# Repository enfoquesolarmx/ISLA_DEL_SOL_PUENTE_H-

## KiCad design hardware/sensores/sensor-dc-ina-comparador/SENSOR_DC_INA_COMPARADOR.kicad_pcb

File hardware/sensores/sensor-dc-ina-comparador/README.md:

# SENSOR_DC_INA_COMPARADOR — módulo de medición, límite y protección de corriente DC

- **Proyecto:** Puente H — prototipo SPWM "Isla del Sol" (inversor 48 V → 127 V / 60 Hz, 1000 W; modo cargador 1 kVA)
- **Módulo:** sensor de corriente del **bus DC**, **bidireccional** (descarga e inyección/carga), con **dos ventanas por hardware**: disparo duro y límite de corriente, más **detección de presencia fail-safe** (SENSOR_OK)
- **Versión:** **V0.2** (serigrafía: `V.0.2/8-NOV-26.J.G`) · **Fecha:** 2026-11-08
- **Estado:** esquemático y layout V0.2 terminados, ERC/DRC sin errores. Pendiente: fabricación y validación en banco
- **Compatible con:** ATmega328P, ATmega4809, STM32, ESP32 y otros MCU de 3.3 V o 5 V, sin cambiar piezas
- **Decisiones que implementa:** [DC-014](../../../docs/decisiones_criticas.md#dc-014-corte-del-pwm-por-hardware-con-lógica-fail-safe-sensor_ok-y-doble-candado) (SENSOR_OK fail-safe) · [DC-016](../../../docs/decisiones_criticas.md#dc-016-corto-circuito-en-ac-niveles-de-protección-arranque-de-motores-arco-transferencia-y-reintentos) (niveles 0 y 1: disparo y límite)
- **Archivos de KiCad (V0.2):** `SENSOR_DC_INA_COMPARADOR_V2.kicad_pro` / `.kicad_sch` / `.kicad_pcb`, con la huella `SSA2512_Littelfuse_Kelvin.kicad_mod` y el modelo `SSA2512_Littelfuse.step`. La V0.1 queda en el historial de Git.
- **Documentos relacionados:** [Corte del PWM por hardware](../../../docs/corte_por_hardware.md) · [Sensado de corriente](../../../docs/sensado_corriente.md)

> **En una línea:** el módulo tiene que decir **"estoy aquí y estoy bien"** todo el tiempo (SENSOR_OK en 0 V). Si se calla por cualquier razón (falla, cable roto, sin alimentación, sobrecorriente), el inversor se apaga por hardware.

*Esquemático explicado del módulo V0.2. En naranja, lo nuevo contra la V0.1: la escalera de 5 resistencias, U4 (límite), Q1 + R6 (SENSOR_OK) y J2-5 = I_LIM. Script: [`img/esquematico_modulo_sensor_dc_u4.py`](img/esquematico_modulo_sensor_dc_u4.py).*

---

## Índice

1. [Qué hace](#1-qué-hace)
2. [Qué cambió en la V0.2](#2-qué-cambió-en-la-v02)
3. [Cómo llegamos aquí](#3-cómo-llegamos-aquí)
4. [Seguridad: qué protege y qué no](#4-seguridad-qué-protege-y-qué-no)
5. [Interfaz](#5-interfaz)
6. [Shunts, umbrales y calibración](#6-shunts-umbrales-y-calibración)
7. [Circuito](#7-circuito)
8. [Layout y serigrafía](#8-layout-y-serigrafía)
9. [Lista de materiales](#9-lista-de-materiales)
10. [Validación en banco](#10-validación-en-banco)
11. [Bitácora](#11-bitácora)
12. [Referencias](#12-referencias)

---

## 1. Qué hace

El módulo se conecta **pegado a los shunts** del bus DC de la tarjeta de potencia y cumple cuatro funciones:

| Función | Salida (J2) | Qué hace con ella la tarjeta de control |
| --- | --- | --- |
| **Medir** la corriente de la batería, en los dos sentidos | **I_OUT** (pin 1): 0–3.3 V, centro 1.67 V | ADC: potencia, eficiencia, control del cargador, pantalla |
| **Proteger** (disparo duro, nivel 0) | **SENSOR_OK** (pin 3): **0 V = todo bien** | R26 + Q_EN cortan EN_HW → 74HC08 apaga los 4 MOSFET en ~2–4 µs, con candado |
| **Detectar presencia** (fail-safe) | La misma **SENSOR_OK** | Sin módulo, sin 15 V o con el cable roto, la línea sube y el inversor no arranca |
| **Limitar** (nivel 1) | **I_LIM** (pin 5): **0 V = en el límite** | D2 del CRÍTICO (interrupción): baja el índice de modulación, sin candado; corren las huellas de corto, arco y motor |

```
              TARJETA DE CONTROL (ATmega328P / 4809 / STM32 / ESP32)
         ▲ I_OUT (ADC)    ▲ SENSOR_OK (R26 → Q_EN → EN_HW)    ▲ I_LIM (D2, INT)
         │                │                                    │
   ┌─────┴────────────────┴────────────────────────────────────┴─────┐
   │ J2 (arriba): 1 I_OUT · 2 GND · 3 SENSOR_OK · 4 GND · 5 I_LIM     │
   │                                                                   │
   │   78L05 · INA240A1 · U3 LM393 (disparo ±105 A) · Q1 BC547         │
   │                      U4 LM393 (límite ±75 A)                      │
   │                                                                   │
   │ J1 (abajo, header): G · K+ · K− · G · X (llave) · 15V             │
   └─────┬──────────────────┬──────────────────────────────────────────┘
         │ IN+ / IN− Kelvin │ 15 V
         ▼                  ▼
   TARJETA DE POTENCIA: 3 shunts de 1 mΩ en paralelo en el bus DC (lado bajo)
```

- **Los shunts se quedan en la tarjeta de potencia** (por ellos pasan hasta 100 A). Al módulo solo llega su voltaje (milivoltios) por dos líneas Kelvin.
- **El módulo es intercambiable**, como los gate drivers: si se daña, se cambia sin tocar la tarjeta de potencia.

---

## 2. Qué cambió en la V0.2

| # | Cambio | Por qué | Decisión |
| --- | --- | --- | --- |
| 1 | **J2-3: FAULT → SENSOR_OK** con **Q1 (BC547) + R6 (10 kΩ)**. FAULT queda interno | Lógica invertida (fail-safe): sin módulo, sin alimentación o con el cable roto, la línea sube y se corta. Con FAULT directo, un sensor ausente "no reportaba falla" | [DC-014](../../../docs/decisiones_criticas.md#dc-014-corte-del-pwm-por-hardware-con-lógica-fail-safe-sensor_ok-y-doble-candado) |
| 2 | **U4 = segundo LM393**: ventana de **límite** (±75 A) | Separar "limitar" de "cortar": un arranque de motor se limita y se clasifica; solo lo peligroso corta | [DC-016](../../../docs/decisiones_criticas.md#dc-016-corto-circuito-en-ac-niveles-de-protección-arranque-de-motores-arco-transferencia-y-reintentos) |
| 3 | **J2-5: NC → I_LIM** (salidas de U4 unidas, colector abierto) | La terminal 5 estaba libre desde la V0.1 | DC-016 |
| 4 | **Escalera de 5 resistencias:** R5 3.6k – **R9 390** – **R10 2.0k** – **R11 390** – R7 3.6k (sale la R6 de 2.7k de la V0.1) | Cuatro umbrales con un solo divisor: las dos ventanas se mueven juntas si el 5 V varía | — |
| 5 | **C8, C9, C10** de 1 nF en los nodos nuevos (C7 sigue en V_ALTO) | Umbrales estables frente al ruido de conmutación | — |
| 6 | **C6** pasa a ser el 0.1 µF de U4; **C5** sigue en U3 | Desacople pegado a cada pin 8 | — |
| 7 | **C14** corregido a la red **5V** (estaba en una red "6V" sin fuente) | Sin esto, la salida del 78L05 quedaba sin capacitor | — |
| 8 | **Resistencias y capacitores THT** (salvo INA240, 78L05, R3, R4 y C3) | Se sueldan y se cambian en la trinchera con cautín común | — |
| 9 | **Serigrafía:** J2 = I_OUT · GND · SEN OK · GND · I_LIM; "C B E" en Q1; "TRENZAR I_OUT, SENSOR_OK E I_LIM CON GND"; versión V.0.2 | Lo primero que lee quien conecta el cable | — |

---

## 3. Cómo llegamos aquí

La V0.1 medía bien y cortaba rápido. Lo que cambió fueron **preguntas de trinchera** que la V0.1 no sabía contestar.

**1. "¿Y si en la trinchera no llega el INA, marcaría FAULT?"** No. FAULT era una señal de **falla activa en 0**: el silencio significaba "todo bien", y un módulo que no está siempre guarda silencio. El inversor habría operado **sin protección y sin que nadie lo supiera**. De ahí salió la lógica invertida: el módulo tiene que estar diciendo "estoy bien" (**SENSOR_OK en 0 V**) para que el inversor opere. Se pidió expresamente que fuera **físico, no firmware**: por eso es un transistor (Q1) en el módulo y otro (Q_EN) en la tarjeta de control, y un jumper rojo (J_RIESGO) para el riesgo autorizado. → DC-014.

**2. "¿El corto en AC se evaluó?"** Al revisar el corto en la salida de 127 V salió que **un arranque de motor y un corto se parecen** en los primeros milisegundos: los dos jalan corriente y hunden el voltaje. Con un solo umbral que corta y enclava, el refrigerador de vacunas habría disparado la protección en cada arranque. La respuesta fueron **niveles**: un límite que recorta sin candado mientras el firmware reconoce la huella (motor, corto o arco), y un disparo duro solo para lo que el firmware no alcanza a seguir. → DC-016.

**3. "¿La detección por firmware evita la chispa del arco?"** No: la chispa inicial no la evita nada electrónico. Lo que sí se controla es **cuánta energía recibe el arco**: con el límite en ±75 A y el corte a ~50 ms, un arco paralelo recibe ~48 J, debajo del criterio de ~100 J con que IEC 62606 fijó los tiempos de los detectores de arco. Eso exige que el límite exista **en hardware**, no solo en el ADC. → DC-016.

**4. La inconsistencia de umbrales.** El disparo duro estaba pensado en 60–80 A, **por debajo** del pico de un arranque de motor (90–140 A en el primario): habría disparado antes de que el firmware pudiera clasificar. Con los **3 shunts de diseño** (0.333 mΩ), la escalera nueva deja el **límite en ±75 A** (1.6 × el pico nominal de 46 A) y el **disparo en ±105 A** (2.3 ×). El límite atrapa el arranque antes de que llegue al disparo.

**5. "El segundo comparador" y una confusión útil.** Se propuso usar "el canal B libre" del LM393 para el límite. Al revisar el esquemático real resultó que **el canal B no estaba libre**: ya cuidaba la sobrecorriente en sentido de carga (la ventana es bidireccional). Por eso el límite lleva **su propio LM393 (U4)** y U3 se quedó intacto.

**6. La revisión antes de fabricar** encontró tres errores que el ERC y el DRC no ven, porque son de función, no de conexión:

| Error | Qué habría pasado |
| --- | --- |
| **U4A con las entradas al revés** (+ en INA_RC) | I_LIM en 0 V todo el tiempo: el CRÍTICO nunca habría dejado subir la modulación |
| **Q1 sin agregar** (FAULT directo a J2-3) | La tarjeta de control nunca habría arrancado: R26 vería la línea en alto |
| **C14 en una red "6V"** | El 78L05 sin capacitor de salida |

> **Lección para la trinchera:** "0 errores" en el DRC significa que las conexiones son coherentes, **no que el circuito haga lo que tiene que hacer**. Antes de fabricar, revisar la función con la tabla de estados (sección 4) y la prueba rápida (sección 10).

---

## 4. Seguridad: qué protege y qué no

### 4.1 Tabla de estados

| Situación | U3 (FAULT) | Q1 | **SENSOR_OK** (J2-3) | U4 | **I_LIM** (J2-5) | Resultado en el inversor |
| --- | --- | --- | --- | --- | --- | --- |
| Corriente normal (entre −75 y +75 A) | suelto | conduce | **0 V** | suelto | alto | Opera |
| Entre 75 y 105 A, en cualquier sentido (arranque, corto naciendo) | suelto | conduce | **0 V** | a 0 V | **0 V** | Límite: el CRÍTICO baja el índice y clasifica (DC-016) |
| Más de 105 A, en cualquier sentido | **a 0 V** | **apagado** | **alto** | a 0 V | 0 V | **Corte en ~2–4 µs + candado** (DC-014) |
| Módulo ausente o cable de J2 roto | — | — | **alto** (R26) | — | alto (R_PU) | **No arranca** |
| Módulo sin 15 V (78L05 apagado) | — | apagado (R6 sin voltaje) | **alto** | — | alto | **No arranca** |
| LM393 U3 quemado abierto o sin chip | — | conduce | 0 V | — | — | ⚠️ Opera **sin disparo duro** (ver 4.2) |
| **Q1 en corto C-E** | — | — | **0 V siempre** | — | — | ⚠️ **Opera sin disparo duro y no se nota** (ver 4.2) |
| U4 dañado o sin chip | — | — | — | — | alto | Sin límite; el disparo duro sigue |

### 4.2 Fallas de una sola pieza que anulan la protección (se dejan escritas a propósito)

- **Q1 en corto colector–emisor:** SENSOR_OK queda en 0 V ("estoy bien") aunque haya sobrecorriente. Es la única falla de una pieza que **anula el disparo duro sin que se note**.
- **U3 sin chip o con la salida abierta:** FAULT nunca baja y Q1 siempre conduce.

Las dos se detectan con la **prueba de disparo** (sección 10, prueba 6). **Debe repetirse en cada mantenimiento** y después de cambiar U3 o Q1. Mientras tanto, el nivel 2 de DC-016 (firmware, con I_OUT y la pinza AC) sigue vigilando, más lento.

### 4.3 Lo que este módulo no hace

- **No es una protección de personas**: no mide fuga a tierra (ver [DC-015](../../../docs/decisiones_criticas.md)).
- **No ve los estados cero** de la modulación híbrida: en ellos la corriente circula dentro del puente sin pasar por el shunt. Como en esos estados la corriente no crece, el disparo llega en el siguiente pulso activo. El sensor AC del primario lo cubre en una versión posterior.
- **I_LIM no es fail-safe a propósito:** sin módulo queda en alto ("sin límite"), pero en ese caso SENSOR_OK ya está cortando. El límite es comodidad para los arranques; la seguridad la dan SENSOR_OK y el disparo duro.
- **No protege el lado DC de la batería**: un corto en los cables de 48 V solo lo interrumpe el **fusible DC clase T junto a la batería**.

---

## 5. Interfaz

### 5.1 J1 — abajo, hacia la tarjeta de potencia (header de 2.54 mm, pegado a los shunts)

| Pin | Señal | Nota |
| --- | --- | --- |
| 1 | GND | Blindaje |
| 2 | **IN+ (Kelvin)** | Desde el pad Kelvin del shunt |
| 3 | **IN− (Kelvin)** | Desde el otro pad; vecino del 2 |
| 4 | GND | Blindaje |
| 5 | **Llave (X)** | **Sin pin ni pad** |
| 6 | 15 V | Alimentación; el módulo genera sus 5 V |

Las señales de milivoltios (2 y 3) quedan entre dos GND y separadas de los 15 V por la llave. En la tarjeta de potencia, la posición 5 del zócalo hembra se **tapa**. El módulo va pegado al shunt con header corto; **nunca cables para IN+ e IN−**.

### 5.2 J2 — arriba, hacia J6 de la tarjeta de control (Phoenix SPT 1,5/5-H-3,5)

| Terminal | Señal | Tipo | Nivel | En la tarjeta de control |
| --- | --- | --- | --- | --- |
| 1 | **I_OUT** | Analógica | 0–3.33 V, centro 1.67 V | ADC (AUX A0, con R 1 kΩ en serie) |
| 2 | GND | | | Trenzar con I_OUT |
| 3 | **SENSOR_OK** | Colector abierto (Q1) | **0 V = sensor bien** | **R26 10 kΩ a 5V → R16 → Q_EN → EN_HW**; también a D3 del AUX (INT1) |
| 4 | GND | | | Trenzar con SENSOR_OK |
| 5 | **I_LIM** | Colector abierto (U4) | **0 V = en el límite** | **R_PU 10 kΩ a 5V → R_S 1 kΩ → D2 del CRÍTICO**, con **C_F 1 nF** a GND |

- **El módulo no pone pull-ups en SENSOR_OK ni en I_LIM:** las pone la tarjeta de control, al voltaje de su MCU. Por eso funciona igual con 5 V (ATmega) que con 3.3 V (STM32, ESP32).
- **Cable:** trenzar I_OUT, SENSOR_OK e I_LIM con GND, corto (< 50 cm) y lejos de la potencia.
- **Tierra:** la tierra del módulo es el lado bajo del shunt. Unión con la tierra de control **en un solo punto**, en el negativo de la batería (ver [corte por hardware](../../../docs/corte_por_hardware.md), sección 10).

### 5.3 Compatibilidad con cualquier MCU

| MCU | I_OUT | SENSOR_OK | I_LIM |
| --- | --- | --- | --- |
| ATmega328P / ATmega4809 (5 V) | ADC: ~680 de 1024 cuentas útiles | R26 + Q_EN + 74HC08 (y D3 del AUX) | D2 del CRÍTICO (INT0 / cualquier pin en el 4809) |
| STM32 (3.3 V) | ADC de 3.3 V, rango completo | BKIN del timer avanzado, **activo en alto** | Entrada de interrupción |
| ESP32 (3.3 V) | ADC con atenuación de 11 dB | Entrada de falla del MCPWM, **activa en alto** | Entrada de interrupción |

---

## 6. Shunts, umbrales y calibración

### 6.1 La pieza

**Littelfuse SSA2512LR001FWR**: 1 mΩ ±1 %, 6 W a 70 °C, lámina metálica, 2512. Huella del proyecto `SSA2512_Littelfuse_Kelvin`. Van en la **tarjeta de potencia**, en el negativo del bus DC. Hoja de datos: [Littelfuse SSA Series](https://www.mouser.com/datasheet/2/240/media-3323775.pdf).

### 6.2 La escalera de umbrales (V0.2)

5 V → R5 3.6 kΩ → **V_ALTO** → R9 390 Ω → **V_LIM_ALTO** → R10 2.0 kΩ → **V_LIM_BAJO** → R11 390 Ω → **V_BAJO** → R7 3.6 kΩ → GND (total 9.98 kΩ)

| Nodo | Voltaje | Distancia a 2.5 V | Comparador |
| --- | --- | --- | --- |
| V_ALTO | 3.196 V | +0.696 V | U3A (+): disparo, descarga |
| V_LIM_ALTO | 3.001 V | +0.501 V | U4A (+): límite, descarga |
| V_LIM_BAJO | 1.999 V | −0.501 V | U4B (−): límite, carga |
| V_BAJO | 1.804 V | −0.696 V | U3B (−): disparo, carga |

El límite queda al **72 %** del disparo. La referencia del INA240 (VS/2) y la escalera salen de los mismos 5 V: si el 78L05 varía ±5 %, todo se mueve junto y los límites casi no cambian.

### 6.3 ¿Cuántas piezas? (1, 2 o 3)

| | 1 pieza | 2 piezas | **3 piezas (diseño, 1000 W)** |
| --- | --- | --- | --- |
| Resistencia efectiva | 1 mΩ | 0.5 mΩ | **0.333 mΩ** |
| Sensibilidad en INA_OUT | 20 mV/A | 10 mV/A | **6.67 mV/A** |
| **Límite (U4, I_LIM)** | ±25 A | ±50 A | **±75 A** |
| **Disparo duro (U3, SENSOR_OK)** | ±35 A | ±70 A | **±105 A** |
| Uso | Primeras pruebas en banco | Pruebas a media potencia | **Operación a 1000 W y arranques de motor** |
| Potencia por pieza a 1000 W (~30 A<sub>rms</sub> en el bus) | ~0.9 W | ~0.23 W | **~0.10 W** |
| Resolución en I_OUT con ATmega (10 bits, 5 V) | ~0.37 A/cuenta | ~0.73 A/cuenta | ~1.1 A/cuenta |
| `R_SHUNT_OHM` en firmware | `0.001` | `0.0005` | `0.000333` |
| Etiqueta CAL del módulo | "CAL: 1 mΩ / ±25 / ±35 A" | "CAL: 0.5 mΩ / ±50 / ±70 A" | **"CAL: 0.33 mΩ / ±75 / ±105 A"** |

**Contra la operación a 1000 W (3 piezas):** el pico nominal en el primario es ~46 A. El límite (75 A) queda a 1.6 × y el disparo (105 A) a 2.3 ×. Un arranque de motor recibe hasta ~12.8 A<sub>rms</sub> en la salida (1.6 × nominal) mientras el límite lo sostiene.

**A medir en la V1** ([DC-016](../../../docs/decisiones_criticas.md)): la inductancia de dispersión del transformador, para conocer el sobretiro sobre los 105 A en los ~4 µs del corte y compararlo con la corriente pulsada (I<sub>DM</sub>) de los IRF100P219.

### 6.4 Reglas de montaje de los shunts

1. **La posición con las pistas Kelvin se monta siempre** (serigrafía "KELVIN · MONTAR SIEMPRE").
2. Las posiciones vacías van como **DNP** en el esquemático.
3. **Cobre simétrico hacia las tres piezas:** si la Kelvin se toma en una sola, la lectura depende de que las tres repartan igual. Calibrar con una corriente conocida.
4. Planos anchos, vías térmicas, lejos de los barrenos de montaje.
5. Serigrafía del valor: **"1mΩ 6W"**, nunca "1M".
6. **Al cambiar el número de piezas:** actualizar `R_SHUNT_OHM`, la etiqueta CAL y los umbrales que espera el firmware.

### 6.5 Fórmulas

| Magnitud | Fórmula |
| --- | --- |
| Salida del INA240 (INA_OUT) | V = 2.5 V + I × R_shunt × 20 |
| Salida al MCU (I_OUT) | V = 1.667 V + I × R_shunt × 13.33 |
| Corriente desde la lectura | **I = (V_I_OUT − 1.667 V) / (R_shunt × 13.33)** |
| Umbral de un nodo de la escalera | V = 5 V × (resistencia de ese nodo a GND) / 9.98 kΩ |
| Corriente de disparo o de límite | **I = (V_nodo − 2.5 V) / (R_shunt × 20)** |

### 6.6 Rango de entrada del LM393

A 5 V, las entradas del LM393 trabajan hasta ~3.5 V (VCC − 1.5 V). Según la hoja de datos, **basta con que una de las dos entradas esté dentro de ese rango** para que la salida sea correcta. Los cuatro umbrales (1.80 a 3.20 V) siempre lo están, así que las ventanas funcionan aunque INA_RC suba hasta ~4.9 V en un corto.

---

## 7. Circuito

### 7.1 Alimentación

| Ref. | Valor | Función |
| --- | --- | --- |
| U1 | L78L05 (SOT-89, cara de abajo) | 15 V → 5 V |
| C15 | 1 µF | Entrada del 78L05 (red 15V) |
| C14 | 1 µF | **Salida del 78L05 (red 5V)** — corregido en la V0.2 |
| C2 | 0.1 µF | Pegado al pin 5 (VS) del INA240 |
| C5 | 0.1 µF | Pin 8 de U3 |
| C6 | 0.1 µF | Pin 8 de U4 |

> **El 78L05 va en la cara de abajo**, que mira hacia la tarjeta de potencia. Verificar que entre las dos tarjetas haya espacio (SOT-89 ≈ 1.6 mm; plástico del header ≈ 2.5 mm) y que no haya un tornillo o un pad de 48 V justo debajo.

### 7.2 Medición (INA240A1, ganancia 20, bidireccional) — sin cambios

```
IN+ (Kelvin) ──[R3 0 Ω]──┬──── IN+ del INA240
                         C3 10 nF (filtro diferencial)
IN− (Kelvin) ──[R4 0 Ω]──┴──── IN− del INA240

VS = 5 V · GND · REF2 = 5 V · REF1 = GND   → referencia = 2.5 V

INA_OUT ──[R1 1 kΩ]──┬──────────── I_OUT (J2-1)
                     ├──[R2 2 kΩ]── GND      (divisor × 0.667)
                     └──[C1 10 nF]─ GND      (filtro)

INA_OUT ──[R8 1 kΩ]──┬── INA_RC              (blanking, τ = 1 µs)
                    [C4 1 nF]
                     │
                    GND
```

Filtro de entrada opcional si en banco hay ruido: R3 = R4 = 10 Ω con C3 = 10 nF C0G. No subir R3/R4 arriba de ~10 Ω (error de ganancia, SBOS662).

### 7.3 Dos ventanas sobre la misma INA_RC

```
U3A (disparo, descarga):  + (3) = V_ALTO      − (2) = INA_RC      → OUT (1) ─┐
U3B (disparo, carga):     + (5) = INA_RC      − (6) = V_BAJO      → OUT (7) ─┴── FAULT (interno)

U4A (límite, descarga):   + (3) = V_LIM_ALTO  − (2) = INA_RC      → OUT (1) ─┐
U4B (límite, carga):      + (5) = INA_RC      − (6) = V_LIM_BAJO  → OUT (7) ─┴── I_LIM (J2-5)
```

*Cómo trabaja un LM393 por dentro: un solo chip con dos comparadores que miran la misma señal del INA, cada uno con su umbral. En la V0.2 hay dos chips así: U3 (disparo) y U4 (límite).*

**Regla para no equivocarse:** en el canal de **descarga** (A), **el umbral va en el +**; en el canal de **carga** (B), **INA_RC va en el +**. Una salida baja cuando su + queda por debajo de su −.

### 7.4 SENSOR_OK (fail-safe)

```
5V ──[R6 10 kΩ]──┬── FAULT (salidas 1 y 7 de U3)
                 │
                 └── base de Q1 (BC547, pin 2)
                     emisor (pin 3) ── GND
                     colector (pin 1) ── SENSOR_OK (J2-3)
```

- **Sin falla:** U3 suelta FAULT, R6 da ~0.43 mA de base, Q1 satura y **SENSOR_OK ≈ 0.1 V**.
- **Con falla:** U3 jala FAULT a 0 V, Q1 se apaga y **la pull-up de la tarjeta de control sube SENSOR_OK** → corte.
- **Sin 15 V:** R6 se queda sin voltaje, Q1 apagado → corte.

### 7.5 Tiempos

| Etapa | Tiempo aprox. |
| --- | --- |
| *Blanking* (R8/C4) | ~1 µs |
| LM393 | ~0.3–1.3 µs |
| Q1 saliendo de saturación | ~0.2–1 µs |
| Q_EN + 74HC08 (tarjeta de control) | ~0.2–0.5 µs |
| Gate driver + descarga de compuerta | ~0.1–0.5 µs |
| **Total del disparo duro** | **~2–4 µs** (estimado, por medir) |
| Límite: hasta la interrupción de D2 (con R_S/C_F de 1 µs) | ~2–3 µs; el CRÍTICO actúa en el siguiente periodo de la portadora (~42 µs) |

---

## 8. Layout y serigrafía

| Cara de componentes (V0.2, zona de J2 y Q1) | Cara de soldadura (V0.2) |
| --- | --- |
|  |  |

| Capa F.Cu | Capa B.Cu |
| --- | --- |
|  |  |

*Esquemático de KiCad V0.2: arriba el INA240A1, el 78L05 y los conectores J1/J2; en medio U3 (disparo), R8/C4 y Q1 con R6; abajo U4 (límite); a la derecha la escalera de umbrales con C7–C10.*

**Lo que se cuidó:**
- **J1 abajo, pegado al shunt; J2 arriba**, hacia la tarjeta de control.
- **IN+ e IN− como par**, encimados en capas opuestas desde J1 hasta R3/R4; C3 pegado al INA240.
- **Q1 y R6 junto a J2-3:** pistas cortas de FAULT a la base y del colector a J2.
- **U4 ruteado sin cruzar la zona del INA**; escalera y capacitores de 1 nF juntos.
- **Planos de GND en las dos caras**, unidos con vías de cosido.
- **J1 sin pad 5 (llave):** el aviso de "huella no coincide con la librería" es esperado. **No usar "Actualizar huellas desde la librería"**: se restaura el pad 5 y se pierde la llave.

**Serigrafía V0.2:**

| Texto | Estado |
| --- | --- |
| J2: I_OUT · GND · SEN OK · GND · I_LIM (las dos caras) | ✅ |
| "TRENZAR I_OUT, SENSOR_OK E I_LIM CON GND" | ✅ |
| "C B E" junto a Q1, "BC547", "10K" | ✅ |
| J1: G · K+ · K− · G · X · 15V | ✅ |
| "SENSOR_DC_INA_COMPARADOR" y "V.0.2/8-NOV-26.J.G" | ✅ |
| "LÍMITE ±75 A" junto a U4 y "DISPARO ±105 A" junto a U3 | ⏳ Sugerido |
| **"CAL: 0.33 mΩ / ±75 / ±105 A"** | ⏳ Sugerido |

### 8.1 Evidencia del proceso: de la V0.1 a la V0.2

Las capturas de KiCad tomadas durante la revisión del 2026-11-08, en orden. Se conservan como evidencia de qué se encontró y cómo se corrigió.

**Paso 1. Esquemático de partida (V0.1).** Una sola ventana (U3) con FAULT directo a J2-3, J2-5 libre y C14 en una red "6V".

**Paso 2. Primer esquemático con U4, escalera de 5 resistencias y THT.** La revisión encontró **U4A con las entradas invertidas** (+ en INA_RC): I_LIM habría quedado en 0 V todo el tiempo. Todavía sin Q1.

| PCB con THT, todavía sin Q1 | 3D con THT, todavía sin Q1 (J2 con "FAULT" y "NC") |
| --- | --- |
|  |  |

**Paso 3. U4A corregido:** + = V_LIM_ALTO, − = INA_RC.

**Paso 4. Q1 (BC547) y R6 agregados.** J2-3 = SENSOR_OK y J2-5 = I_LIM en el esquemático. La serigrafía de J2 todavía tenía los nombres viejos y se corrigió después (sección 8).

**Paso 5. V0.2 terminada:** las capturas de la sección 8 (J2 y Q1, capas F.Cu y B.Cu, cara inferior con "V.0.2/8-NOV-26.J.G" y esquemático de KiCad).

**Referencia: la V0.1 como estaba en el repositorio**

| Cara de componentes V0.1 | Cara de soldadura V0.1 |
| --- | --- |
|  |  |

> **Para que las imágenes se vean**, la carpeta `img/` debe estar junto a este README (en GitHub: `hardware/sensores/sensor-dc-ina-comparador/img/`). Para leerlo sin GitHub o imprimirlo: `sensor_dc_v02.pdf`, con todas las imágenes incluidas.

---

## 9. Lista de materiales

| Ref. | Valor / parte | Encapsulado | Función |
| --- | --- | --- | --- |
| U1 | L78L05 | SOT-89 | Regulador de 5 V |
| U2 | **INA240A1PW** (ganancia 20) | TSSOP-8 | Amplificador de corriente bidireccional |
| U3 | **LM393** | DIP-8 | Ventana de **disparo duro** |
| **U4** | **LM393** | DIP-8 | Ventana de **límite** (nuevo) |
| **Q1** | **BC547** | TO-92 | SENSOR_OK (nuevo) |
| R1, R8 | 1 kΩ | THT | Divisor de I_OUT / *blanking* |
| R2 | 2 kΩ | THT | Divisor de I_OUT |
| R3, R4 | 0 Ω (10 Ω con filtro) | SMD | Entrada del INA240 |
| R5, R7 | 3.6 kΩ | THT | Escalera (extremos) |
| **R6** | **10 kΩ** | THT | **Base de Q1** (en la V0.1, R6 era el 2.7 kΩ de la escalera) |
| **R9, R11** | **390 Ω** | THT | Escalera (nuevo) |
| **R10** | **2.0 kΩ** | THT | Escalera (nuevo) |
| C1 | 10 nF | THT | Filtro de I_OUT |
| C2, C5, **C6** | 0.1 µF | THT / SMD | Desacople INA240, U3, **U4** |
| C3 | 10 nF C0G | SMD | Filtro diferencial |
| C4 | 1 nF ("102") | THT | *Blanking* |
| C7, **C8, C9, C10** | 1 nF ("102") | THT | Umbrales V_ALTO, **V_LIM_ALTO, V_LIM_BAJO, V_BAJO** |
| C14, C15 | 1 µF | THT | Salida (5V) y entrada (15V) del 78L05 |
| J1 | Header macho 1 × 6, 2.54 mm, **sin pin 5** | THT | A la tarjeta de potencia |
| J2 | Phoenix SPT 1,5/5-H-3,5 | THT | A J6 de la tarjeta de control |
| *(tarjeta de potencia)* | Littelfuse SSA2512LR001FWR × 3 | 2512 | Shunts del bus DC |

**En la tarjeta de control** (no en este módulo): R26 10 kΩ, R16 10 kΩ, Q_EN BC547 y J_RIESGO para SENSOR_OK; **R_PU 10 kΩ, R_S 1 kΩ y C_F 1 nF** para I_LIM en D2.

---

## 10. Validación en banco

**Prueba rápida al armar** (solo el módulo, 15 V en J1-6, sin corriente en el shunt; pull-ups de prueba de 10 kΩ a 5 V en J2-3 y J2-5):

| # | Medir | Esperado |
| --- | --- | --- |
| 1 | 5V (salida del 78L05) | 4.8–5.2 V |
| 2 | INA_OUT / I_OUT | ~2.5 V / ~1.67 V |
| 3 | V_ALTO · V_LIM_ALTO · V_LIM_BAJO · V_BAJO | 3.20 · 3.00 · 2.00 · 1.80 V (±2 %) |
| 4 | FAULT (base de Q1) | ~0.7 V |
| 5 | **J2-3 SENSOR_OK** | **< 0.2 V** |
| 6 | **J2-5 I_LIM** | **~5 V** (si da 0 V: revisar las entradas de U4A) |
| 7 | Quitar los 15 V | J2-3 sube a ~5 V (corte) |

**Pruebas de función:**

| # | Prueba | Esperado |
| --- | --- | --- |
| 1 | **Ganancia y signo:** 5, 10 y 20 A por el shunt, en los dos sentidos, contra una pinza de referencia | I_OUT según la fórmula; positivo = descarga |
| 2 | **Límite sin potencia:** inyectar voltaje en INA_RC (a través de R8, con el INA240 sin alimentar o desconectado) | I_LIM cae en ~3.00 V y en ~2.00 V |
| 3 | **Disparo sin potencia:** igual, subiendo más | SENSOR_OK sube en ~3.20 V y en ~1.80 V |
| 4 | **Presencia:** desconectar J2 con la tarjeta de control encendida | El inversor no arranca (EN_HW < 0.3 V) |
| 5 | **Disparo real a bajo voltaje:** bus de 12–24 V, fuente con límite, sobrecorriente controlada | Del cruce del umbral al apagado de las compuertas: **< 3–4 µs** (osciloscopio) |
| 6 | **Prueba de mantenimiento (Q1 y U3):** puentear FAULT a GND con el equipo encendido a bajo voltaje | **SENSOR_OK debe subir y el inversor cortar.** Si no corta: Q1 en corto o U3 dañado. **No operar hasta corregir** |
| 7 | **Ruido de conmutación:** inversor operando, ver INA_RC e I_LIM en el osciloscopio | Sin flancos falsos en I_LIM. Si los hay: filtro de entrada (R3 = R4 = 10 Ω, C3 = 10 nF) o histéresis de 1 MΩ de cada salida de U4 a su + |

---

## 11. Bitácora

| Fecha | Qué se hizo | Resultado | Siguiente paso |
| --- | --- | --- | --- |
| 2026-11-04 | Definición del módulo (INA240 + LM393 en ventana), interfaz J1/J2, esquemático y layout | Medición y protección validadas en esquemático | Serigrafía, DRC final |
| 2026-11-04 | Shunts definidos: Littelfuse SSA2512LR001FWR (1 mΩ, 6 W), configuraciones de 1, 2 y 3 piezas | — | Validar en banco |
| 2026-11-08 | **SENSOR_OK fail-safe:** Q1 BC547 + R6 10 kΩ; J2-3 deja de ser FAULT (DC-014) | Sin módulo, sin 15 V o con el cable roto, el inversor no arranca | — |
| 2026-11-08 | **U4 (segundo LM393) para el límite ±75 A**, escalera de 5 resistencias, J2-5 = I_LIM (DC-016) | Disparo ±105 A y límite ±75 A con los 3 shunts de diseño | — |
| 2026-11-08 | Revisión antes de fabricar: U4A con entradas invertidas, Q1 faltante, C14 en "6V" | Corregidos. ERC/DRC sin errores | Fabricar V0.2 |
| 2026-11-08 | Resistencias y capacitores a THT; serigrafía V.0.2/8-NOV-26.J.G | Listo para Gerbers | Validación en banco (sección 10) |
| 2026-11-08 | Archivos de KiCad V0.2 en el repositorio; verificación de redes en la PCB: U3 (1/7 FAULT, 3 V_ALTO, 6 V_BAJO), U4 (1/7 I_LIM, 3 V_LIM_ALTO, 6 V_LIM_BAJO), Q1 (1 SENSOR_OK, 2 FAULT, 3 GND), J2 (1 I_OUT · 3 SENSOR_OK · 5 I_LIM), C14 en 5V | Coinciden con el diseño | Fabricar |

---

## 12. Referencias

1. Texas Instruments, *INA240* (SBOS662): amplificador de corriente bidireccional, −4 V a 80 V, rechazo mejorado al PWM.
2. Texas Instruments, *LM393 Dual Differential Comparator*: salida de colector abierto, rango de modo común hasta VCC − 1.5 V, salida correcta mientras una entrada esté dentro del rango; respuesta ~1.3 µs. <https://www.ti.com/lit/ds/symlink/lm393.pdf>
3. onsemi, *BC546B, BC547A/B/C, BC548B/C* (BC546-D): hFE mínimo 110, V<sub>CE(sat)</sub>, orden de patas TO-92 (1 = C, 2 = B, 3 = E). <https://www.onsemi.com/pdf/datasheet/bc546-d.pdf>
4. STMicroelectronics, *L78L05*.
5. Littelfuse, *SSA Series* (shunts de lámina metálica). <https://www.mouser.com/datasheet/2/240/media-3323775.pdf>
6. BEAMA, *AFDD FAQ fact sheet*: tiempos de IEC 62606 y criterio de ~100 J. <https://www.beama.org.uk/static/84330bcd-90bc-4fe3-87df9d092ec14b89/BEAMA-ARC-FAULT-DETECTION-AFDD-FAQ-Fact-Sheet.pdf>
7. Documentos del proyecto: [decisiones críticas](../../../docs/decisiones_criticas.md) (DC-014, DC-016) · [corte por hardware](../../../docs/corte_por_hardware.md) · [sensado de corriente](../../../docs/sensado_corriente.md).

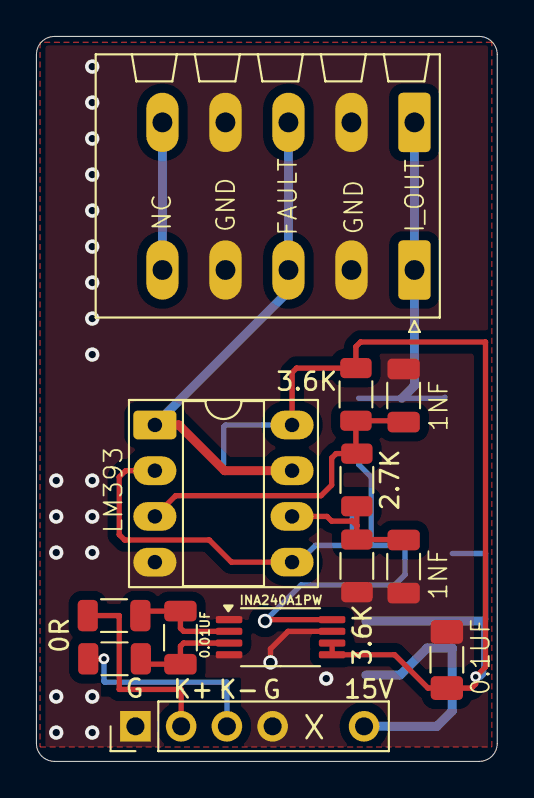
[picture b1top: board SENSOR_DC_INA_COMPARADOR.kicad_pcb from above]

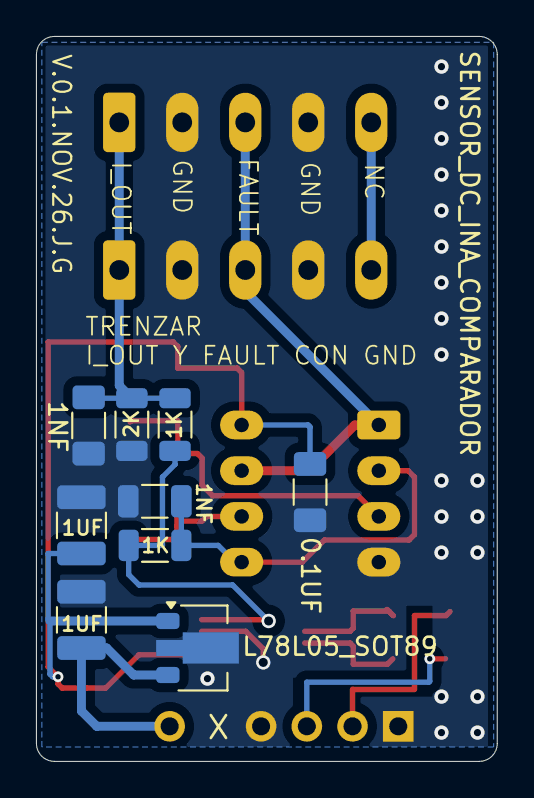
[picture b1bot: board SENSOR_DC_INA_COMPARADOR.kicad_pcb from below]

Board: 2 copper layers, 25.6 x 40.3 mm, 22 parts (9 on the bottom side), 13 nets.

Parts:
C1: 0.01UF; C_1206_3216Metric_Pad1.33x1.80mm_HandSolder
C2, C5: 0.1UF; C_1206_3216Metric_Pad1.33x1.80mm_HandSolder
C3: 0.01UF; C_1206_3216Metric
C4, C6, C7: 0.001UF/1NF-102; C_1206_3216Metric
C14, C15: 1UF; C_1210_3225Metric_Pad1.33x2.70mm_HandSolder
J1: INPUT_INA; PinHeader_1x06_P2.54mm_Vertical
J2: SALIDA; PhoenixContact_SPT_1.5_5-H-3.5_1x05_P3.5mm_Horizontal
R1, R8: 1K; R_1206_3216Metric
R2: 2K; R_1206_3216Metric
R3, R4: 0; R_1206_3216Metric
R5, R7: 3.6K; R_1206_3216Metric
R6: 2.7K; R_1206_3216Metric
U1: L78L05_SOT89; SOT-89-3
U2: INA240A1PW; TSSOP-8_4.4x3mm_P0.65mm
U3: LM393; DIP-8_W7.62mm_Socket_LongPads

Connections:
5V: C2.1, C5.1, C14.1, R5.2, U1.1 (OUT), U2.5 (V+), U2.6 (REF2), U3.8 (V+)
15V: C15.1, J1.6, U1.3 (IN)
FAULT: J2.3, U3.1, U3.7
GND: C1.2, C2.2, C4.2, C5.2, C6.1, C7.1, C14.2, C15.2, J1.1, J1.4, J2.2, J2.4, R2.1, R7.1, U1.2 (GND), U2.1 (GND), U2.4 (GND), U2.7 (REF1), U3.4 (V-)
IN+ (Kelvin): J1.2, R3.1
IN- (Kelvin): J1.3, R4.1
INA_OUT: R1.1, R8.1, U2.8
INA_RC: C4.1, R8.2, U3.2 (-), U3.5 (+)
I_OUT: C1.1, J2.1, R1.2, R2.2
unnamed: C3.1, R3.2, U2.2 (+)
unnamed: C3.2, R4.2, U2.3 (-)
V_ALTO: C7.2, R5.1, R6.2, U3.3 (+)
V_BAJO: C6.2, R6.1, R7.2, U3.6 (-)
